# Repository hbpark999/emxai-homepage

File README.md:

This is a [Next.js](https://nextjs.org) project bootstrapped with [`create-next-app`](https://nextjs.org/docs/app/api-reference/cli/create-next-app).

## Getting Started

First, run the development server:

```bash
npm run dev
# or
yarn dev
# or
pnpm dev
# or
bun dev
```

Open [http://localhost:3000](http://localhost:3000) with your browser to see the result.

You can start editing the page by modifying `app/page.tsx`. The page auto-updates as you edit the file.

This project uses [`next/font`](https://nextjs.org/docs/app/building-your-application/optimizing/fonts) to automatically optimize and load [Geist](https://vercel.com/font), a new font family for Vercel.

## Learn More

To learn more about Next.js, take a look at the following resources:

- [Next.js Documentation](https://nextjs.org/docs) - learn about Next.js features and API.
- [Learn Next.js](https://nextjs.org/learn) - an interactive Next.js tutorial.

You can check out [the Next.js GitHub repository](https://github.com/vercel/next.js) - your feedback and contributions are welcome!

## Deploy on Vercel

The easiest way to deploy your Next.js app is to use the [Vercel Platform](https://vercel.com/new?utm_medium=default-template&filter=next.js&utm_source=create-next-app&utm_campaign=create-next-app-readme) from the creators of Next.js.

Check out our [Next.js deployment documentation](https://nextjs.org/docs/app/building-your-application/deploying) for more details.

## Remote MCP and PDN surrogate

The Vercel application exposes the remote MCP endpoint at:

```text
https://www.emxai.net/api/mcp
```

PDN tools use a separate Cloud Run inference service in
`services/pdn-decap-surrogate`. Configure these server-only Vercel variables:

```text
PDN_SURROGATE_API_URL=https://YOUR-CLOUD-RUN-URL
PDN_SURROGATE_API_TOKEN=<shared Cloud Run application token>
```

The browser-only training GUI is available at `/web-tools/pdn-decap`; students
do not need Python. Deployment and model-definition details are in
`services/pdn-decap-surrogate/README.md`.

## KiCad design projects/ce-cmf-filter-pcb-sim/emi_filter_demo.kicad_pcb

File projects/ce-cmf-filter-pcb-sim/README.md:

# CE-CMF-Filter-PCB Sim — desktop snapshot

최신 모델: **80-case-2026-09-09**, GPR/PCA8, 150 kHz–30 MHz, 201점 CM/DM 크기.
현재 GUI와 대표 4포트 SPICE, PCB B2 S14P, RLC 예제를 이 폴더에 독립 복사했다.
환경 키, HFSS 프로젝트, 대용량 solver/RAW 결과는 포함하지 않았다. `snapshot.json`에서 원본 파일 hash를 확인한다.

## Windows에서 실행

Python 3.13 (Tkinter 포함), LTspice를 준비하고 이 폴더에서 실행한다.

```powershell
python -m venv .venv
.\.venv\Scripts\python -m pip install -r requirements.txt
.\.venv\Scripts\python scripts/launch_circuit_gui.py
```

LTspice 기본 경로는 `C:\Program Files\ADI\LTspice\LTspice.exe`다.
다르면 `src/netlist.py`와 `mvp/cmc_surrogate_gui.py`의 `LTSPICE` 경로를 수정한다.
특성 예측·기본 예제 해석에는 HFSS나 Claude API 키가 필요하지 않다.
`config.py`에 남은 기존 PC의 HFSS/환경파일 경로는 이 데모에서 사용하지 않으며 새 해석 자동화 전에 재설정한다.

`scripts/verify_circuit_gui.py`는 실제 LTspice 6건을 실행한다. 먼저 `reports/charts` 폴더를 만든다.
모델은 포함된 신뢰 가능한 pickle만 읽는다. 사용자 pickle 업로드를 허용하지 않는다.

## 범위

- 특성 예측, SPICE 예제, PCB/필터 RLC 편집, 회로도, 대표 모델 CE 고조파 RMS 비교.
- 현재 대표 SPICE는 1종이며 임의 surrogate 입력의 위상/4포트 모델이 아니다.
- SPICE 변환 CM 최대 1.814%, DM 0.058%는 검사 지점의 변환 오차이며 surrogate 일반화 오차가 아니다.
- QP/AVG 검파·CE 인증, DC/시간영역 검증 완료로 표현하지 않는다.
- 예제 `.cir`는 단독 실행 전체 netlist가 아니라 앱이 CMC/LISN/소스를 붙이는 회로 조각이다.

웹 작업은 저장소 루트 `docs/ce-cmf-filter-pcb-sim-handoff.md`를 따른다.
후속 8~12건 해석·재학습·평가가 필요하며 이번 버전에는 포함하지 않았다.

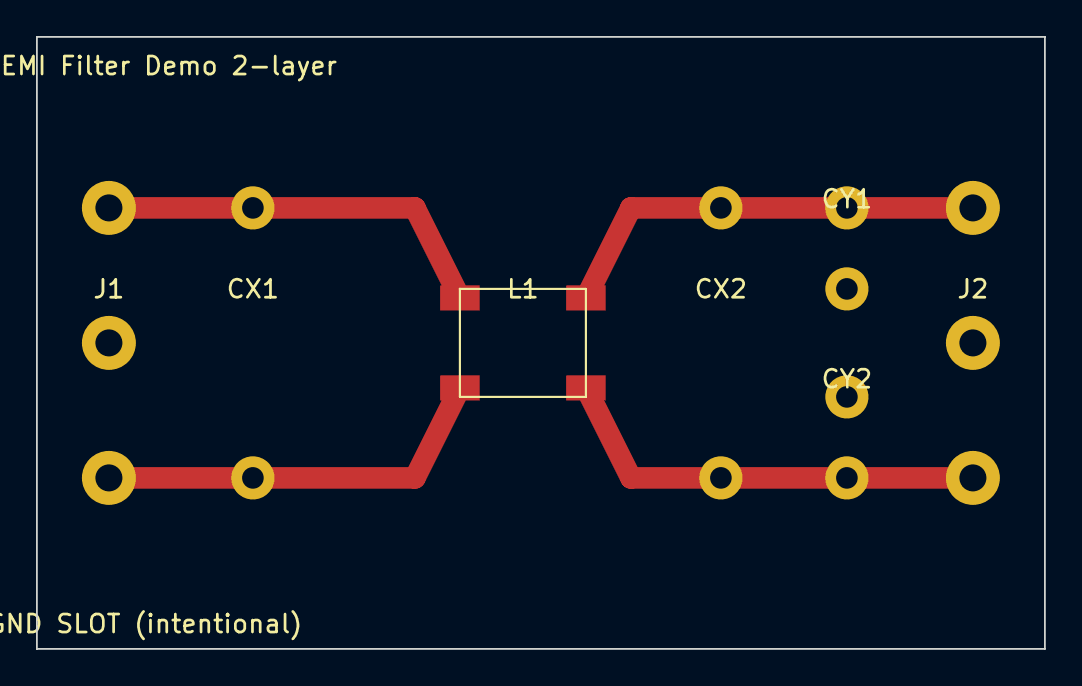
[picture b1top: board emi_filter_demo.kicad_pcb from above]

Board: 2 copper layers, 56.0 x 34.0 mm, 7 parts (0 on the bottom side), 5 nets.

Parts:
CX1: 4.7uF X2
CX2: 1.5uF X2 (opt)
CY1, CY2: 100nF Y2
J1: AC_IN
J2: AC_OUT
L1: ACM7060-701

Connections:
L_IN: CX1.1, J1.1, L1.1
L_OUT: CX2.1, CY1.1, J2.1, L1.2
N_IN: CX1.2, J1.2, L1.3
N_OUT: CX2.2, CY2.1, J2.2, L1.4
PE: CY1.2, CY2.2, J1.3, J2.3
